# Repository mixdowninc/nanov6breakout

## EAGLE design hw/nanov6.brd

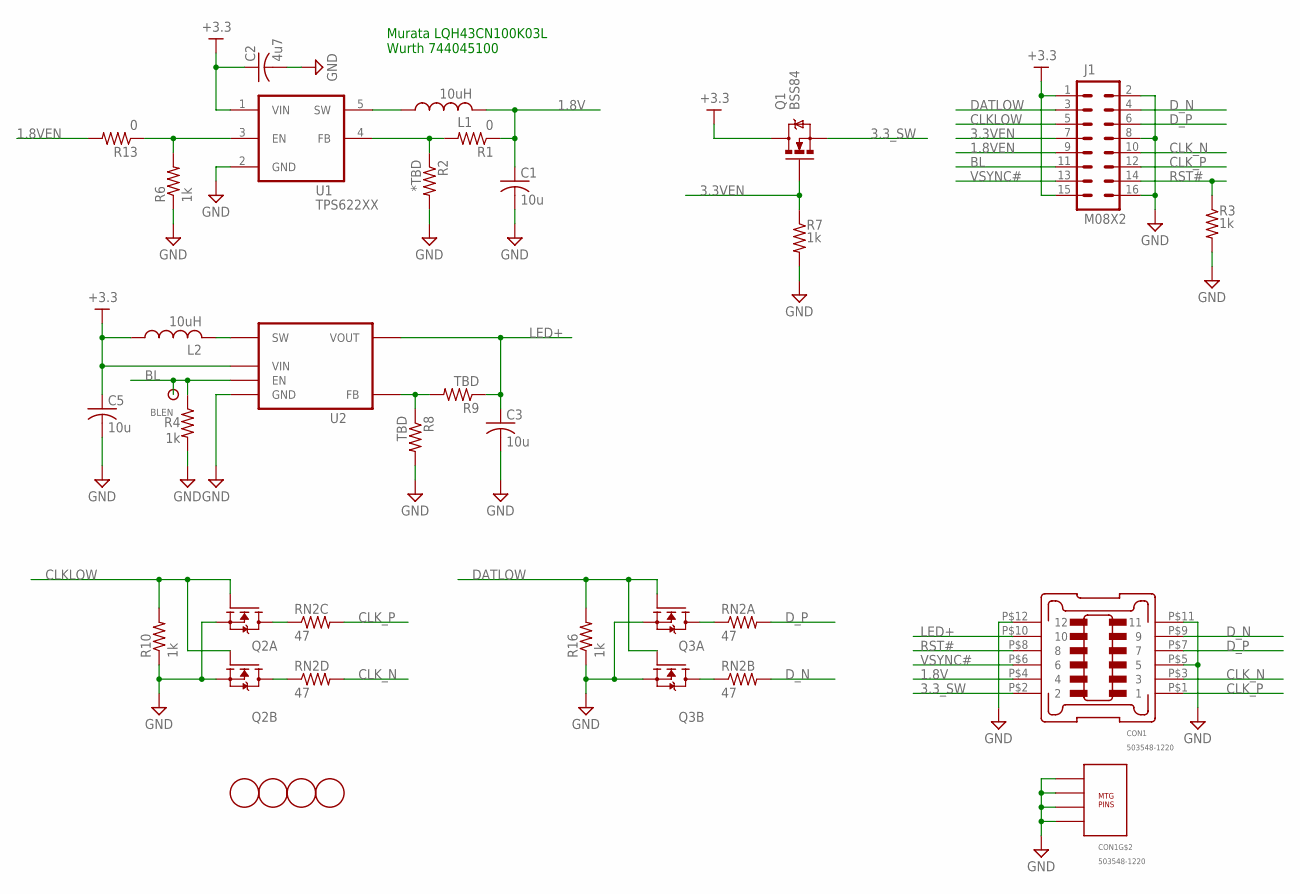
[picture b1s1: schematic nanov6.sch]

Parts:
BLEN: TESTPOINTKEYSTONE_5016; 5016
C1, C3, C5: 10u; C0805
C2: 4u7; C0805
CON1: 503548-1220
J1: M08X2; 2X8
L1, L2: 10uH; L1812
Q1: BSS84; SOT23-3
Q2, Q3: 2N7002SC70-6; SC70-6
R1, R13: 0; R0805
R2: *TBD; R0805
R3, R4, R6, R7, R10, R16: 1k; R0805
R8, R9: TBD; R0805
RN2: 47; 2008
U1: TPS622XX; SOT23-5
U2: TLV61220; SOT23-6
U$2, U$3, U$11, U$15: MOUNTING_HOLE125; HOLE_MTG_125

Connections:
1.8V: C1.1, CON1.P$4 (4), L1.2, R1.1
1.8VEN: J1.9, R13.2
3.3VEN: J1.7, Q1.1 (G), R7.1
3.3_SW: CON1.P$2 (2), Q1.2 (S)
+3.3: C2.1, C5.1, J1.1, J1.15, L2.1, Q1.3 (D), U1.1 (VIN), U2.6 (VIN)
BL: BLEN.P$1, J1.11, R4.1, U2.3 (EN)
CLKLOW: J1.5, Q2.2 (G), Q2.5 (G), R10.2
CLK_N: CON1.P$3 (3), J1.10, RN2.5 (2)
CLK_P: CON1.P$1 (1), J1.12, RN2.6 (2)
DATLOW: J1.3, Q3.2 (G), Q3.5 (G), R16.2
D_N: CON1.P$9 (9), J1.4, RN2.7 (2)
D_P: CON1.P$7 (7), J1.6, RN2.8 (2)
GND: C1.2, C2.2, C3.2, C5.2, CON1.MTG1, CON1.MTG2, CON1.MTG3, CON1.MTG4, CON1.P$5 (5), CON1.P$11 (11), CON1.P$12 (12), J1.2, J1.8, J1.16, Q2.1 (S), Q2.4 (S), Q3.1 (S), Q3.4 (S), R2.2, R3.2, R4.2, R6.1, R7.2, R8.2, R10.1, R16.1, U1.2 (GND), U2.2 (GND)
LED+: C3.1, CON1.P$10 (10), R9.1, U2.5 (VOUT)
unnamed: R6.2, R13.1, U1.3 (EN)
unnamed: L1.1, U1.5 (SW)
unnamed: L2.2, U2.1 (SW)
unnamed: R8.1, R9.2, U2.4 (FB)
unnamed: Q2.3 (D), RN2.3 (1)
unnamed: Q2.6 (D), RN2.4 (1)
unnamed: Q3.3 (D), RN2.1
unnamed: Q3.6 (D), RN2.2 (1)
unnamed: R1.2, R2.1, U1.4 (FB)
RST#: CON1.P$8 (8), J1.14, R3.1
VSYNC#: CON1.P$6 (6), J1.13

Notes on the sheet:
Murata LQH43CN100K03L Wurth 744045100

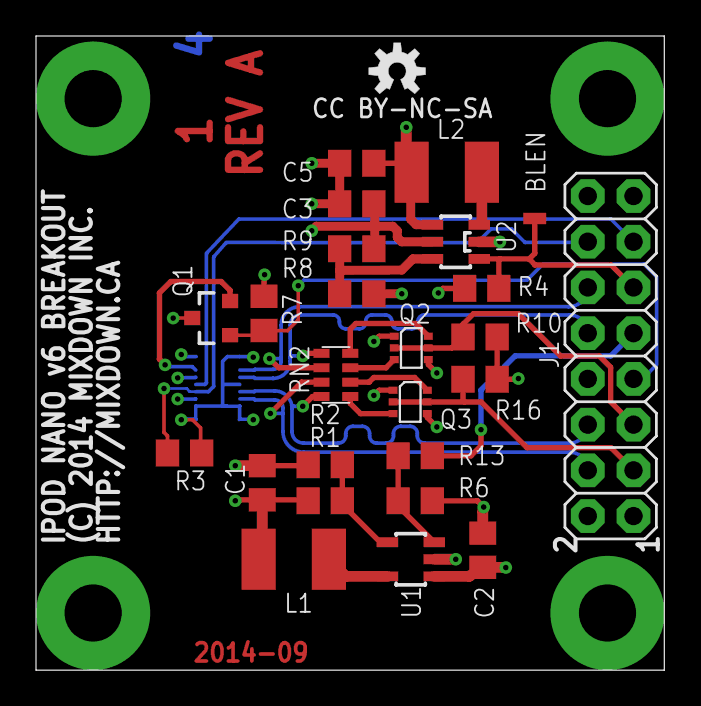
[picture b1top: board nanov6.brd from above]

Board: 4 copper layers, 34.9 x 35.2 mm, 30 parts (1 on the bottom side), 25 nets.

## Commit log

2014-02-28 initial design
2014-03-01 added .gitignore
2014-03-02 add pulldown to RST#, make 3.3VEN active-high. Resolves #471, refs #469.
2014-03-02 add pulldown to BLEN. Resolves #469.

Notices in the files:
hw/nanov6.brd:
(C) 2014 MIXDOWN INC.
CC BY-NC-SA
parts and their libraries:
SparkFun: Licensing: CC v3.0 Share-Alike You are welcome to use this library for commercial purposes.
